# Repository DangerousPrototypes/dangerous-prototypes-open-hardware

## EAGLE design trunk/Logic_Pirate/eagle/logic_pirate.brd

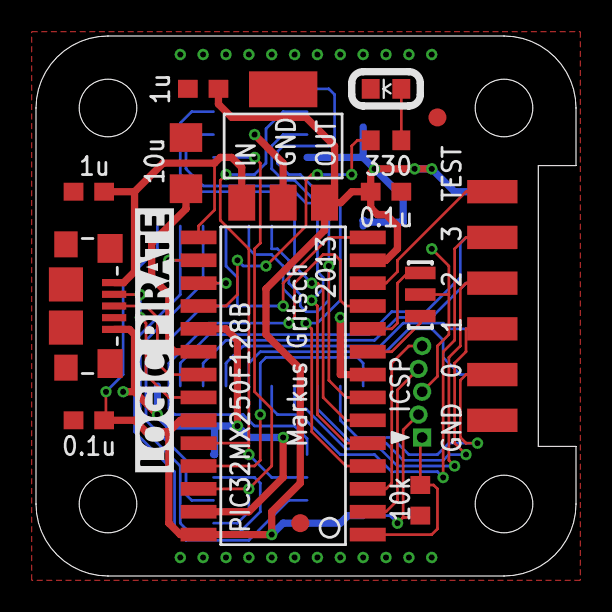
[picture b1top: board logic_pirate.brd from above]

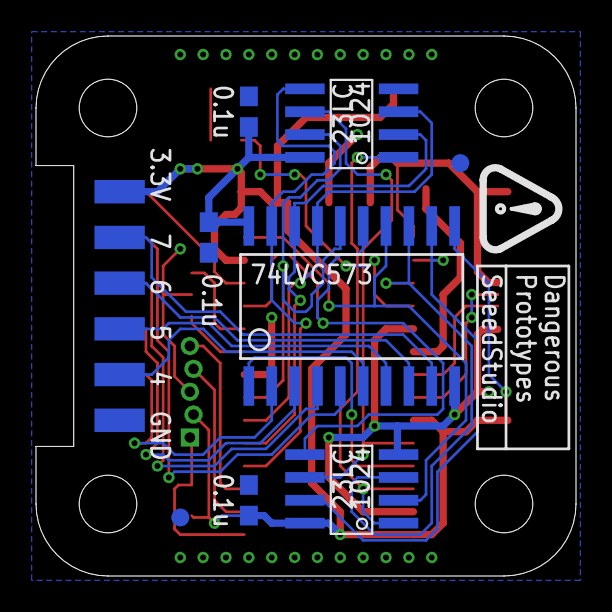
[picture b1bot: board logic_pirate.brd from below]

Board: 2 copper layers, 30.0 x 30.0 mm, 28 parts (10 on the bottom side), 33 nets.

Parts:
C1, C2: 1u; DP_DEVICES_C603
C3: 10u; C1206
C4, C5, C6, C7, C8: 100n; DP_DEVICES_C603
IC1: TINYLOGIC_PIC32MX250F128BSO; TINYLOGIC_DP_DEVICES_SOIC-28W
IC2, IC3: TINYLOGIC_DP_DEVICES_IC_MEM_23LC1024; TINYLOGIC_DP_DEVICES_SOIC-8
IC4: TINYLOGIC_DP_DEVICES_IC_74LVC573; TINYLOGIC_DP_DEVICES_SOIC-20
J1, J2: DP_DEVICES_CON_HEADER_1X06-SMD-RIGHT-ANGLED; DP_DEVICES_M1X6_MALE_RIGHT_ANGLED_SMD
JP1: TINYLOGIC_CHIPKIT_UNO32_MECHANICAL_HDR-1X5-OFFSET; TINYLOGIC_CHIPKIT_UNO32_MECHANICAL_HDR-1X6_OFFSET
JP2, JP3, JP4, JP5: FIDUCIAL1X2; FIDUCIAL-1X2
LED1: Status; CHIPKIT_UNO32_DISCRETE_D0603
PCB1: TINYLOGIC_DP_DEVICES_PCB_DP_SQUARE-3X3; TINYLOGIC_DP_DEVICES_DP3030_V1
R1: 10k; DP_DEVICES_R603
R2: 330; DP_DEVICES_R603
U$1: LP_LOGO
U$4: TINY_LOGO
USB: DP_DEVICES_CON-USB-F-MICRO-B; DP_DEVICES_CONN_USB_MICRO-B
VREG1: MCP1825S-3302E/DB; DP_DEVICES_SOT-223
X1: RESONATORSMD; RESONATOR-SMD

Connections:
BUF_!OE!: IC1.25, IC4.1
D0: IC1.4, IC3.5, IC4.19
D1: IC1.5, IC3.2, IC4.18
D2: IC1.6, IC3.3, IC4.17
D3: IC1.7, IC3.7, IC4.16
D4: IC1.11, IC2.5, IC4.15
D5: IC1.14, IC2.2, IC4.14
D6: IC1.17, IC2.3, IC4.13
D7: IC1.16, IC2.7, IC4.12
D+: IC1.21, USB.P3
D-: IC1.22, USB.P2
GND: C1.2, C2.2, C3.2, C4.2, C5.2, C6.2, C7.2, C8.2, IC1.8, IC1.19, IC1.27, IC2.4, IC3.4, IC4.10, J1.6, J2.1, JP1.3, LED1.C, USB.P5, VREG1.2, VREG1.4, X1.2
LED(OC3): IC1.18, R2.2
MCLR: IC1.1, JP1.1, R1.1
unnamed: IC4.2, J1.5
unnamed: IC4.3, J1.4
unnamed: IC4.4, J1.3
unnamed: IC4.5, J1.2
unnamed: IC4.6, J2.2
unnamed: IC4.7, J2.3
unnamed: IC4.8, J2.4
unnamed: IC4.9, J2.5
unnamed: LED1.A, R2.1
unnamed: IC1.10, X1.3
unnamed: IC1.9, X1.1
unnamed: C3.1, IC1.20
PGEC: IC1.3, JP1.5
PGED: IC1.2, JP1.4
RAM_!CS!: IC1.26, IC2.1, IC3.1
RAM_SCK(REFCLKO): IC1.24, IC2.6, IC3.6
TEST(OC4): IC1.12, J1.1
VBUS: C1.1, IC1.15, USB.P1, VREG1.1
VCC: C2.1, C4.1, C5.1, C6.1, C7.1, C8.1, IC1.13, IC1.23, IC1.28, IC2.8, IC3.8, IC4.11, IC4.20, J2.6, JP1.2, R1.2, VREG1.3
